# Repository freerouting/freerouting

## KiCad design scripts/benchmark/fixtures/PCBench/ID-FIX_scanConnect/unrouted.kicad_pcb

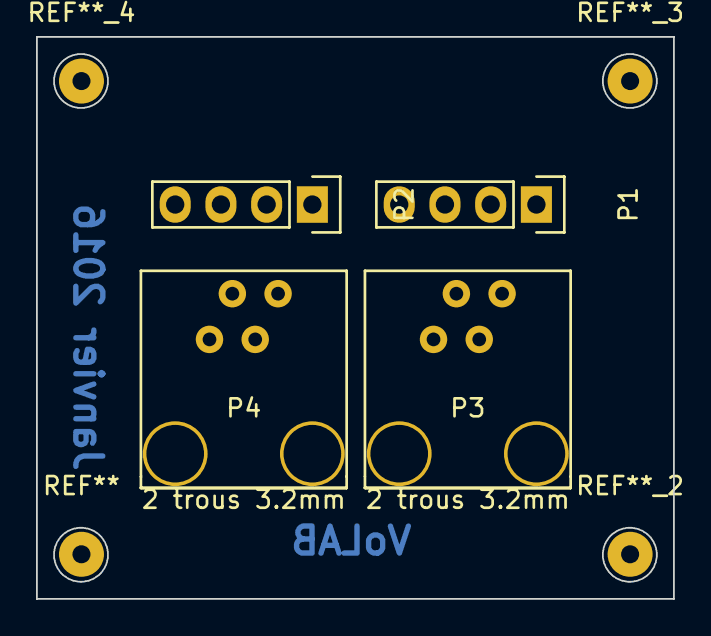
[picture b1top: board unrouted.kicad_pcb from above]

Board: 2 copper layers, 35.4 x 31.2 mm, 4 parts (0 on the bottom side), 6 nets, no tracks yet.

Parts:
P1, P2: CONN_01X04; Pin_Header_Straight_1x04
P3, P4: RJ9

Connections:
/COILA_A: P1.1, P3.1
/COILA_B: P1.2, P3.2
/COILB_A: P1.3, P3.3
/COILB_B: P1.4, P3.4
/GND: P2.2, P2.3, P4.2
/VCC: P2.1, P2.4, P4.1

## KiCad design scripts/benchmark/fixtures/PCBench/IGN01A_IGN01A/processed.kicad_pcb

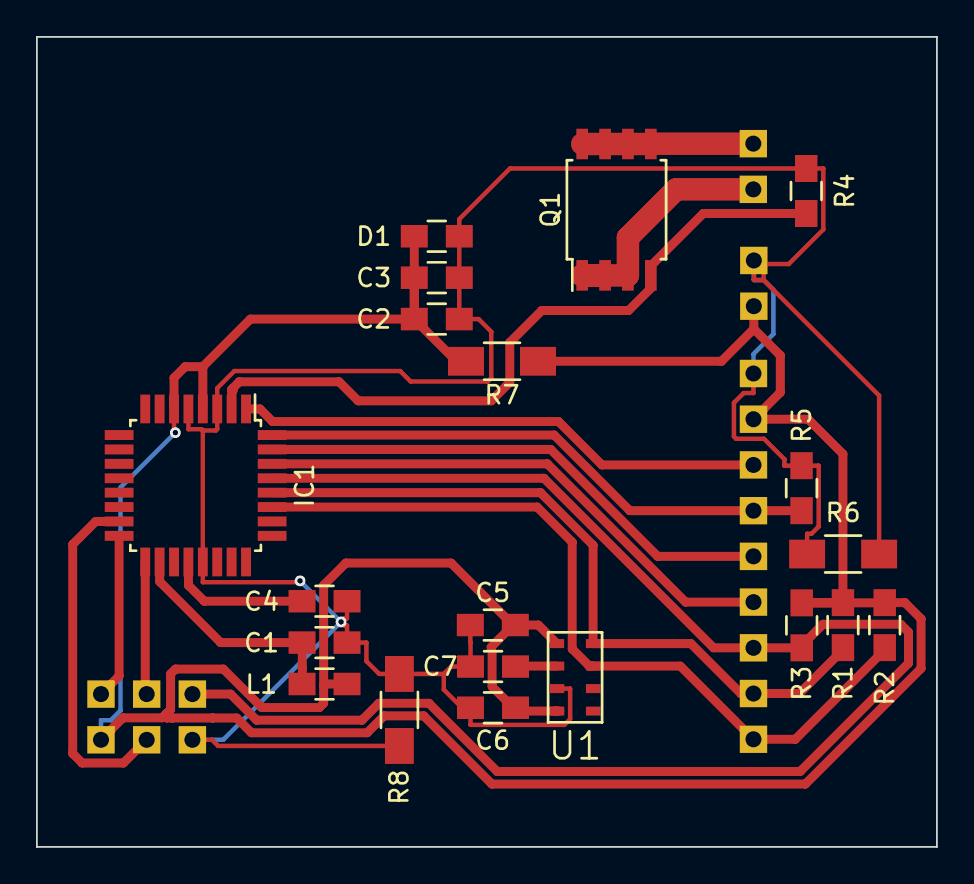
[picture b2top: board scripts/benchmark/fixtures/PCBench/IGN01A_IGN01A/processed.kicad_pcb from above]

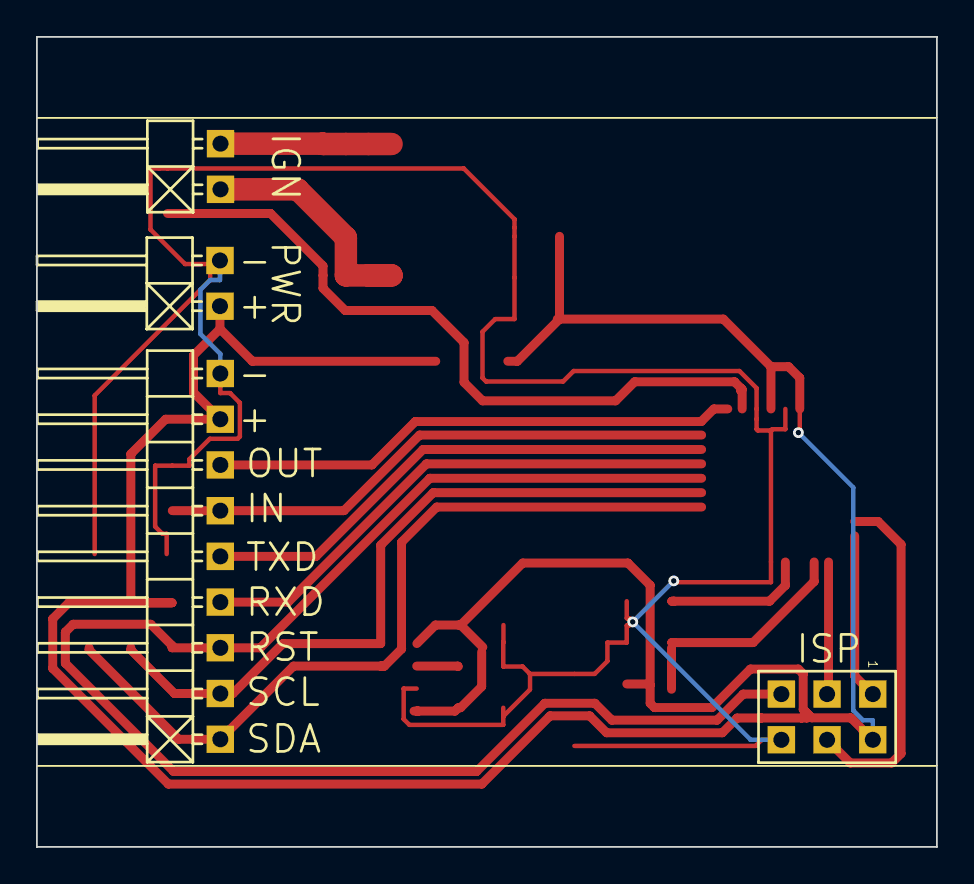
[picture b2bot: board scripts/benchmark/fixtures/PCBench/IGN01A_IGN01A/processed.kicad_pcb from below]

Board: 2 copper layers, 50.0 x 45.0 mm, 24 parts (4 on the bottom side), 18 nets.

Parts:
C1, C2, C4, C6, C7: 100nF; C_0805_HandSoldering
C3: 22uF/6.3V; C_0805_HandSoldering
C5: 10uF; C_0805_HandSoldering
D1: 1N4007; C_0805_HandSoldering
IC1: ATMEGA328-A; TQFP-32_7x7mm_Pitch0.8mm
J1: PWR; Angled_1x02
J2: IGN; Angled_1x02
J3: HEADER_1x09; Angled_1x09
J5: ISP; Straight_2x03
L1: 10uH; C_0805_HandSoldering
Q1: IRF7413ZPBF; SOIJ-8_5.3x5.3mm_Pitch1.27mm
R1, R2, R3, R4, R5: 10k; C_0805_HandSoldering
R6, R7, R8: 0; C_1206_HandSoldering
U1: MPL3115A2; LGA-MPL3115A

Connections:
/IGN: IC1.2, Q1.4, R4.1
/IN: IC1.32, J3.6, R5.1
/MISO: IC1.16, J5.1
/MOSI: IC1.15, J5.4
/OUT: IC1.1, J3.7
/RST: IC1.29, J3.3, J5.5, R3.2
/RXD: IC1.30, J3.4
/SCK: IC1.17, J5.3
/SCL: IC1.28, J3.2, R1.2, U1.8
/SDA: IC1.27, J3.1, R2.2, U1.7
/TXD: IC1.31, J3.5
GND: C1.2, C2.2, C3.2, C4.2, C5.2, C6.2, C7.2, D1.2, IC1.3, IC1.5, IC1.21, J1.2, J3.9, J5.6, R4.2, R5.2, R6.1, R6.2, R8.1, R8.2, U1.3
unnamed: C4.1, IC1.20
unnamed: C7.1, U1.2
unnamed: J2.1, Q1.1, Q1.2, Q1.3
unnamed: J2.2, Q1.5, Q1.6, Q1.7, Q1.8
VAA: C1.1, IC1.18, L1.1
VDD: C2.1, C3.1, C5.1, C6.1, D1.1, IC1.4, IC1.6, J1.1, J3.8, J5.2, L1.2, R1.1, R2.1, R3.1, R7.1, R7.2, U1.1, U1.4

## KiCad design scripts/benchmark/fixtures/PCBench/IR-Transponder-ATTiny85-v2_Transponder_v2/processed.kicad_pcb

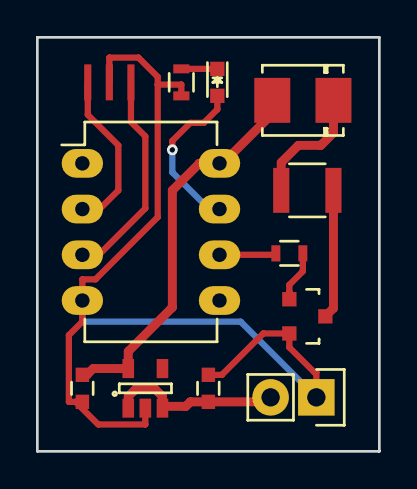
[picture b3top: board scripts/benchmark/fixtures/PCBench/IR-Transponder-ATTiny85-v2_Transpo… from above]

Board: 2 copper layers, 19.0 x 23.0 mm, 12 parts (0 on the bottom side), 11 nets.

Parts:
C1, C2: .1u; C_0603
D1: LED; DO-214BA
D2: LED; LED_0603
IC1: ATTINY85-S; DIP-8_W7.62mm_LongPads
P1: CONN_01X02; Pin_Header_Straight_1x02
Q1: NMOS; SOT-23
R1, R3: 470; R_0603
R2: 100; R_1210
U1: 5.5v Reg; SOT-23-5
X1: CRYSTAL_SMD; myResonator

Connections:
+5V: C2.1, D1.2, IC1.8, U1.5
GND: C1.2, C2.2, IC1.4, P1.1, Q1.2, R3.2, U1.2, X1.3
unnamed: C1.1, P1.2, U1.1, U1.3
unnamed: D1.1, R2.1
unnamed: D2.1, R3.1
unnamed: IC1.2, X1.1
unnamed: IC1.3, X1.2
unnamed: Q1.1, R1.2
unnamed: Q1.3, R2.2
PB1: IC1.6, R1.1
PB2: D2.2, IC1.7

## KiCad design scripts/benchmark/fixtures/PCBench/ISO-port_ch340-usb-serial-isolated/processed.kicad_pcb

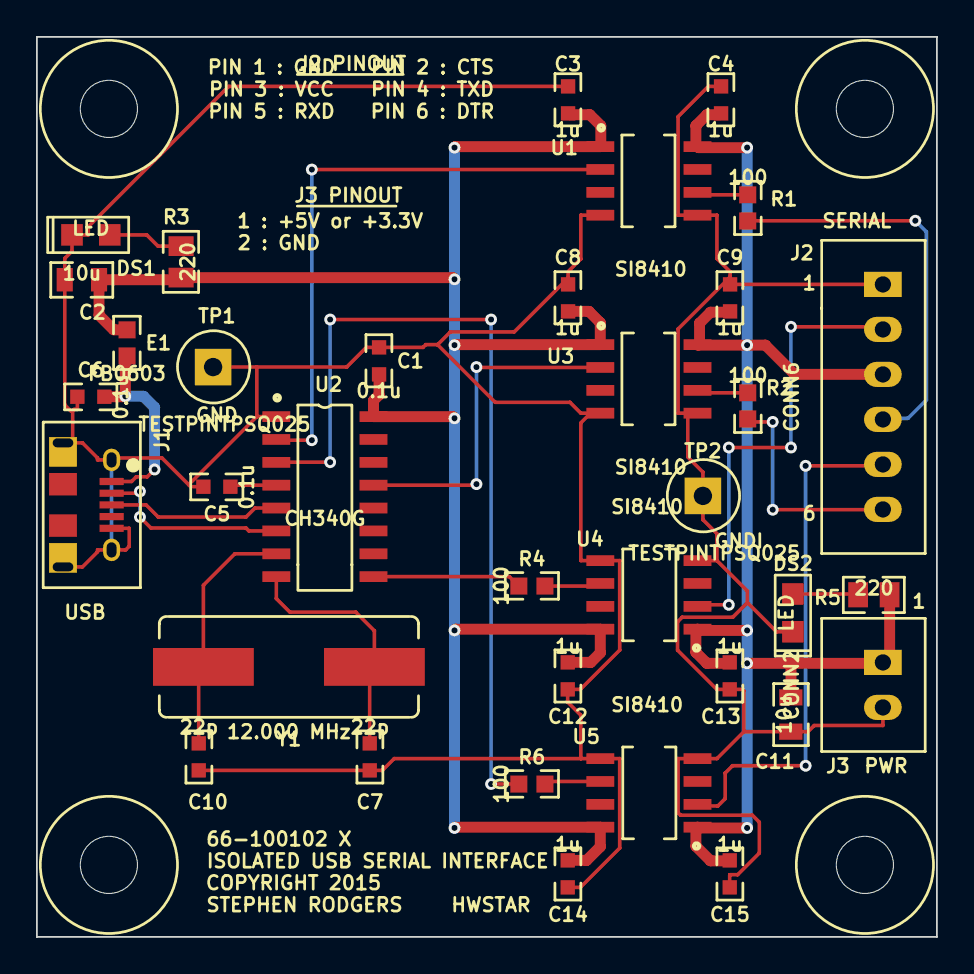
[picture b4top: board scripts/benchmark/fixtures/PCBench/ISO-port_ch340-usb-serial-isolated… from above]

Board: 2 copper layers, 50.0 x 50.0 mm, 39 parts (0 on the bottom side), 24 nets.

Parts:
C1, C5, C6: 0.1u; CC0603
C2, C11: 10u; CC0805
C3, C4, C8, C9, C12, C13, C14, C15: 1u; CC0603
C7, C10: 22p; CC0603
DS1, DS2: LED; LED0805
E1: FB0603; RC0603
J1: CONN-USB-B-MICRO-FCI-11018194
J2: CONN6; JST_B6B_XH_A
J3: CONN2; JST_B2B_XH_A
MTG-HOLE-125-RING-300, MTG-HOLE-125-RING-300_2, MTG-HOLE-125-RING-300_3, MTG-HOLE-125-RING-300_4: VAL**; MTG-HOLE-125-RING-300
R1, R2, R4, R6: 100; RC0603
R3, R5: 220; RC0805
TP1, TP2: TESTPINTPSQ025; TESTPIN
U1, U3, U4, U5: SI8410; SOIC8N-SI8410
U2: CH340G; SOIC16N-SAR
Y1: 12.000 MHz; HC49US-SAR

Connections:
+5V: C1.1, C2.1, C3.1, C8.1, C12.1, C14.1, E1.2, R3.1, U1.1, U2.16, U3.1, U4.8, U5.8
+5VI: C4.1, C9.1, C11.1, C13.1, C15.1, J2.3, J3.1, R5.1, U1.8, U3.8, U4.1, U5.1
/CTSI: J2.2, U4.2
/CTSU: R4.1, U2.9
/D+: J1.3, U2.5
/D-: J1.2, U2.6
/DTRI: J2.6, R2.2
/DTRU: U2.13, U3.2
/RXDI: J2.5, U5.2
/RXDU: R6.1, U2.3
/TXDI: J2.4, R1.2
/TXDU: U1.2, U2.2
/VBUS: C6.1, E1.1, J1.1
GND: C1.2, C2.2, C3.2, C5.2, C6.2, C7.2, C8.2, C10.2, C12.2, C14.2, DS1.2, J1.5, J1.6, J1.7, J1.8, J1.9, TP1.1, U1.4, U2.1, U3.4, U4.5, U5.5
GNDI: C4.2, C9.2, C11.2, C13.2, C15.2, DS2.2, J2.1, J3.2, TP2.1, U1.5, U3.5, U4.4, U5.4
unnamed: R1.1, U1.6
unnamed: R6.2, U5.6
unnamed: DS2.1, R5.2
unnamed: DS1.1, R3.2
unnamed: R2.1, U3.6
unnamed: R4.2, U4.6
unnamed: C10.1, U2.7, Y1.1
unnamed: C5.1, U2.4
unnamed: C7.1, U2.8, Y1.2

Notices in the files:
scripts/benchmark/fixtures/PCBench/ISO-port_ch340-usb-serial-isolated/processed.kicad_pcb:
COPYRIGHT 2015
